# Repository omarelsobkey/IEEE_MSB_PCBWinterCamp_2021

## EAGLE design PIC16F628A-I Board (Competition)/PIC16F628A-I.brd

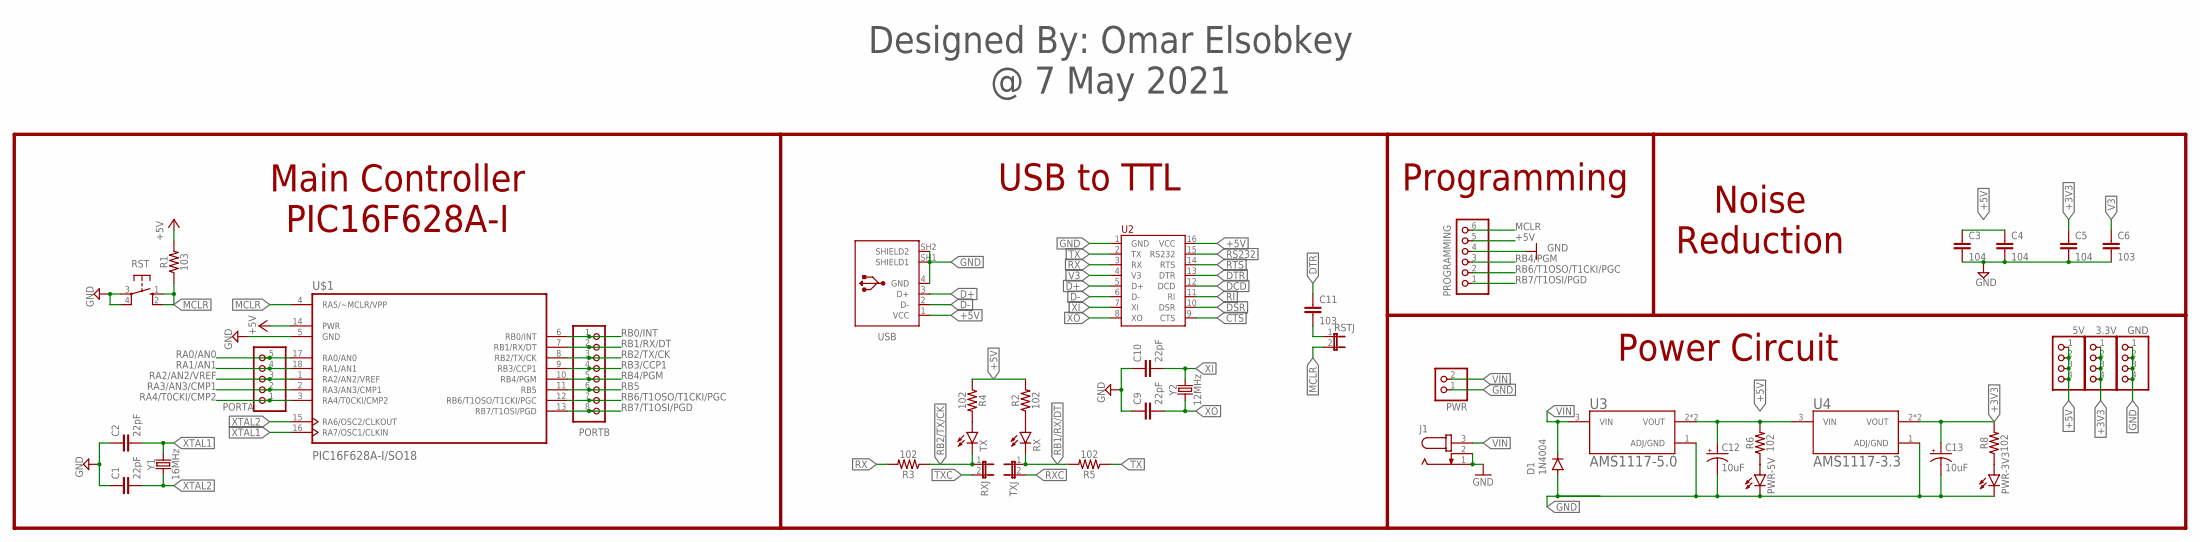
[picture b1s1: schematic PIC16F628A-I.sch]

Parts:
3.3V, 5V: PINHD-1X4; 1X04
C1, C2, C9, C10: 22pF; CAP-PTH-2.54
C3, C4, C5: 104; CAP-PTH-2.54
C6, C11: 103; CAP-PTH-2.54
C12, C13: 10uF; CPOL-RADIAL-2.5MM-5MM-KIT
D1: 1N4004; DO41-10
GND: PINHD-1X4; 1X04
J1: JACK-PLUG0; SPC4077
PORTA: PINHD-1X5; 1X05
PORTB: PINHD-1X8; 1X08
PROGRAMMING: PINHD-1X6; 1X06
PWR: PINHD-1X2; 1X02
PWR-3V3, PWR-5V: LEDCHIP-LED0805; CHIP-LED0805
R1: 103; 1206
R2, R3, R4, R5, R6, R8: 102; 1206
RST: 10-XX; B3F-10XX
RSTJ: JP1E; JP1
RX: LEDCHIP-LED0805; CHIP-LED0805
RXJ: JP1E; JP1
TX: LEDCHIP-LED0805; CHIP-LED0805
TXJ: JP1E; JP1
U2: CH340G; SOP-16
U3: AMS1117-5.0
U4: AMS1117-3.3; AMS1117-5.0
U$1: PIC16F628A-I/SO18; SOIC127P1030X265-18N
USB: 61729-1011; 61729-1011BLF
Y1: 16MHz; HC49U
Y2: 12MHz; HC49U

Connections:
+3V3: 3.3V.1, 3.3V.2, 3.3V.3, 3.3V.4, C5.1, C13.1 (+), R8.2, U4.2 (VOUT), U4.4 (VOUT)
+5V: 5V.1, 5V.2, 5V.3, 5V.4, C3.1, C4.1, C12.1 (+), PROGRAMMING.5, R1.2, R2.2, R4.1, R6.2, U2.16 (VCC), U3.2 (VOUT), U3.4 (VOUT), U4.3 (VIN), U$1.14 (PWR), USB.1 (VCC)
CTS: U2.9 (CTS)
D+: U2.5 (D+), USB.3 (D+)
D-: U2.6 (D-), USB.2 (D-)
DCD: U2.12 (DCD)
DSR: U2.10 (DSR)
DTR: C11.1, U2.13 (DTR)
GND: C1.1, C2.1, C3.2, C4.2, C5.2, C6.2, C9.1, C10.1, C12.2 (-), C13.2 (-), D1.A, GND.1, GND.2, GND.3, GND.4, J1.1, J1.2, PROGRAMMING.4, PWR.1, PWR-3V3.C, PWR-5V.C, RST.3, RST.4 (P1), U2.1 (GND), U3.1 (ADJ/GND), U4.1 (ADJ/GND), U$1.5 (GND), USB.4 (GND), USB.SH1 (SHIELD1), USB.SH2 (SHIELD2)
MCLR: PROGRAMMING.6, R1.1, RST.1 (S), RST.2 (S1), RSTJ.2, U$1.4 (RA5/~MCLR/VPP)
unnamed: R2.1, RX.A
unnamed: R4.2, TX.A
unnamed: PWR-5V.A, R6.1
unnamed: PWR-3V3.A, R8.1
unnamed: C11.2, RSTJ.1
RA0/AN0: PORTA.5, U$1.17 (RA0/AN0)
RA1/AN1: PORTA.4, U$1.18 (RA1/AN1)
RA2/AN2/VREF: PORTA.3, U$1.1 (RA2/AN2/VREF)
RA3/AN3/CMP1: PORTA.2, U$1.2 (RA3/AN3/CMP1)
RA4/T0CKI/CMP2: PORTA.1, U$1.3 (RA4/T0CKI/CMP2)
RB0/INT: PORTB.1, U$1.6 (RB0/INT)
RB1/RX/DT: PORTB.2, R5.2, RX.C, TXJ.1, U$1.7 (RB1/RX/DT)
RB2/TX/CK: PORTB.3, R3.1, RXJ.1, TX.C, U$1.8 (RB2/TX/CK)
RB3/CCP1: PORTB.4, U$1.9 (RB3/CCP1)
RB4/PGM: PORTB.5, PROGRAMMING.3, U$1.10 (RB4/PGM)
RB5: PORTB.6, U$1.11 (RB5)
RB6/T1OSO/T1CKI/PGC: PORTB.7, PROGRAMMING.2, U$1.12 (RB6/T1OSO/T1CKI/PGC)
RB7/T1OSI/PGD: PORTB.8, PROGRAMMING.1, U$1.13 (RB7/T1OSI/PGD)
RI: U2.11 (RI)
RS232: U2.15 (RS232)
RTS: U2.14 (RTS)
RX: R3.2, U2.3 (RX)
RXC: TXJ.2
TX: R5.1, U2.2 (TX)
TXC: RXJ.2
V3: C6.1, U2.4 (V3)
VIN: D1.C, J1.3, PWR.2, U3.3 (VIN)
XI: C10.2, U2.7 (XI), Y2.2
XO: C9.2, U2.8 (XO), Y2.1
XTAL1: C2.2, U$1.16 (RA7/OSC1/CLKIN), Y1.2
XTAL2: C1.2, U$1.15 (RA6/OSC2/CLKOUT), Y1.1

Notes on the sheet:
Main Controller PIC16F628A-I
USB to TTL
Programming
Noise Reduction
Power Circuit
Designed By: Omar Elsobkey @ 7 May 2021

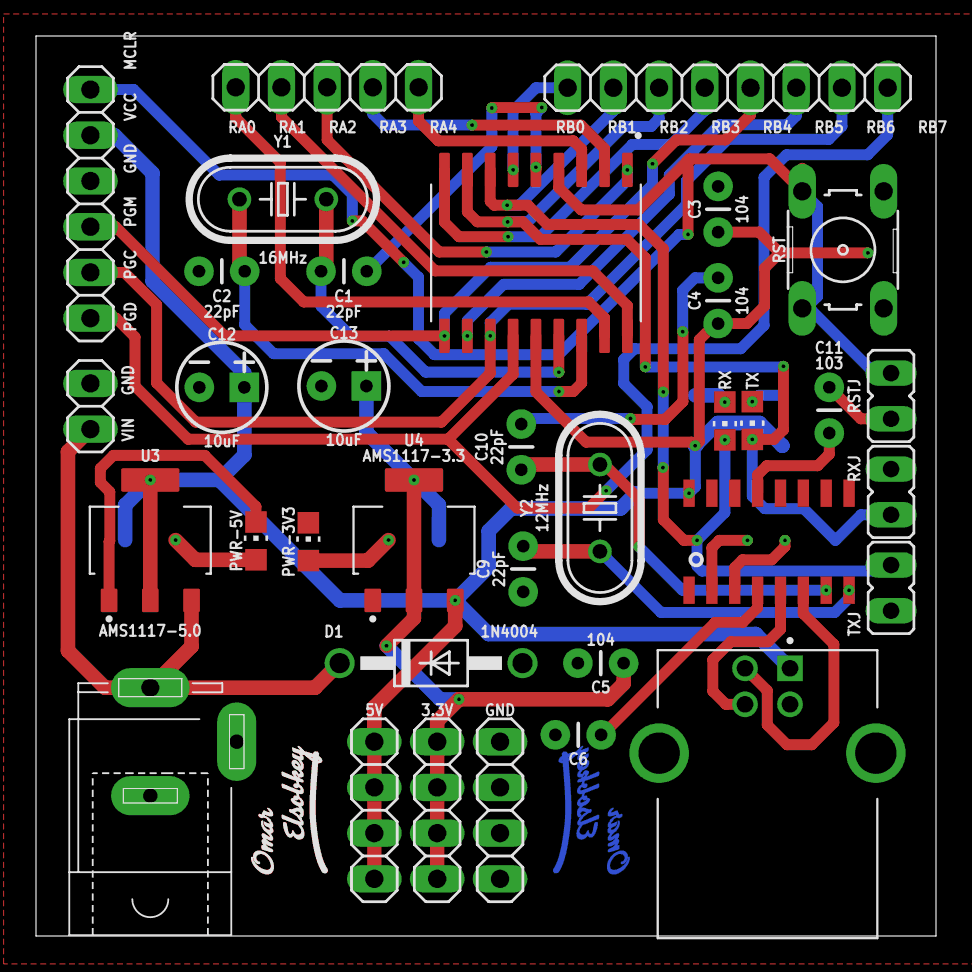
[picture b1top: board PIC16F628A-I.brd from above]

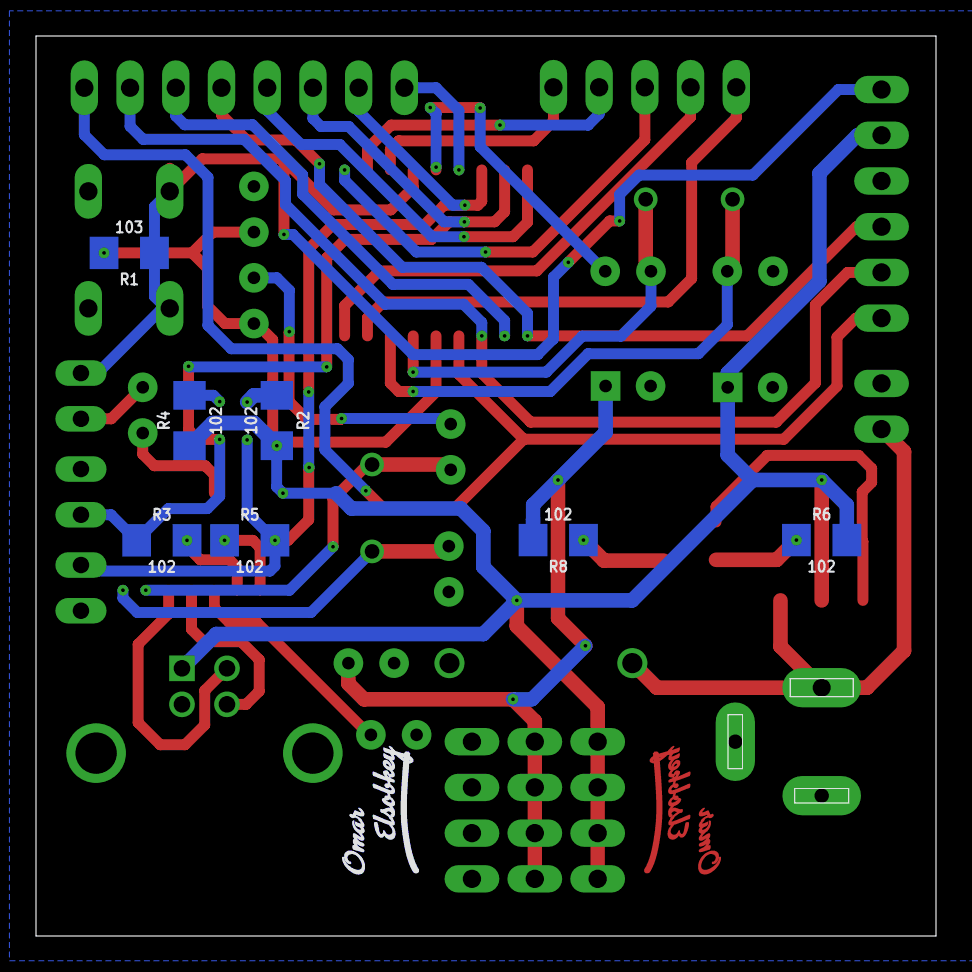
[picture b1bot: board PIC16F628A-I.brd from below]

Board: 2 copper layers, 50.0 x 50.0 mm, 46 parts (9 on the bottom side), 33 nets.

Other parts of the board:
U$2, U$3: OMAR_ELSOBKEY_X0.5_TN
U$4, U$5: OMAR_ELSOBKEY_X0.5_T

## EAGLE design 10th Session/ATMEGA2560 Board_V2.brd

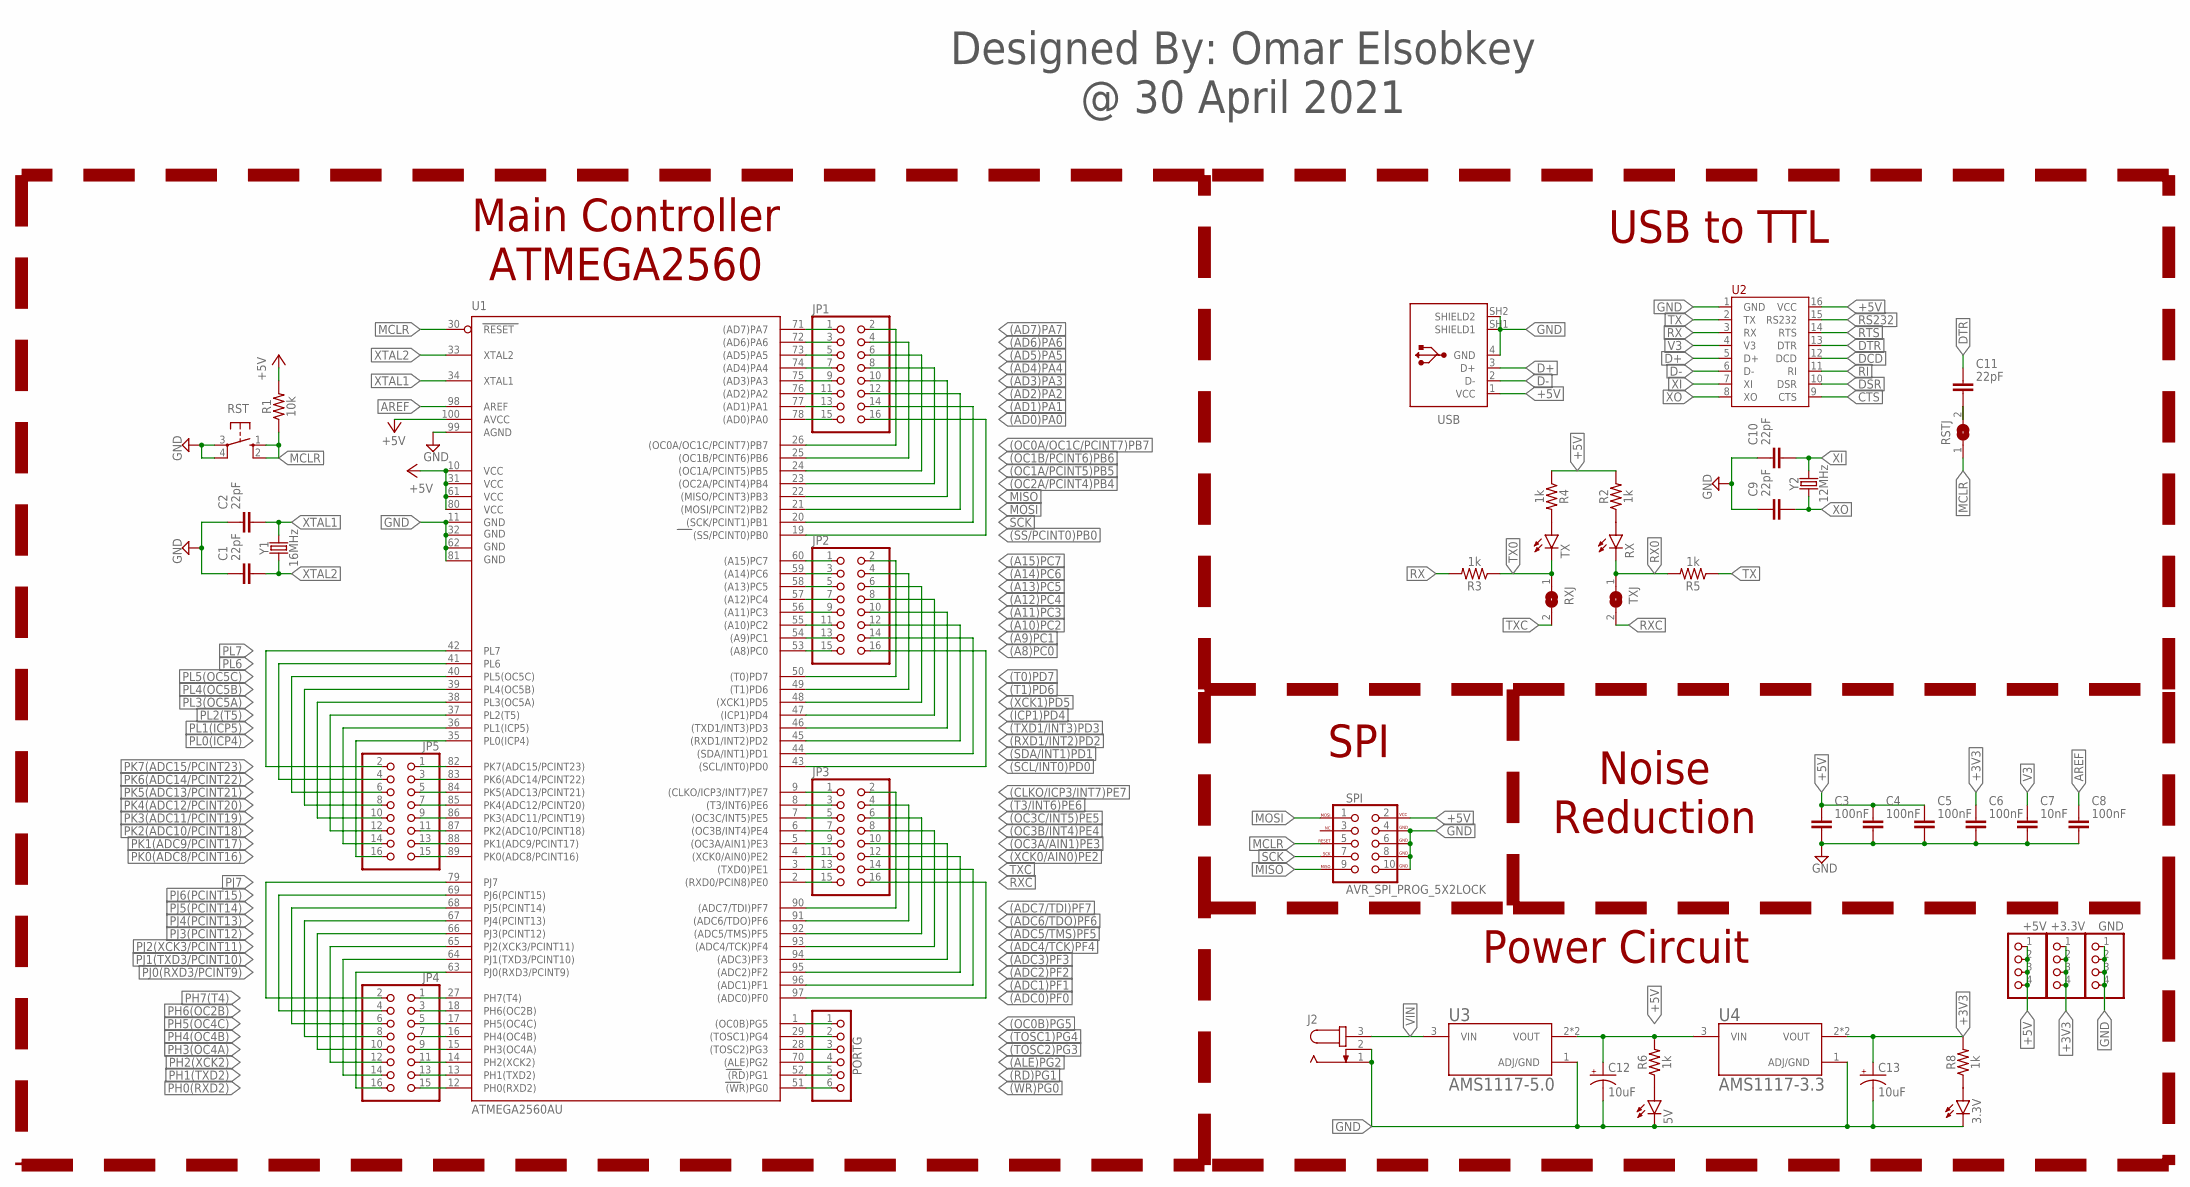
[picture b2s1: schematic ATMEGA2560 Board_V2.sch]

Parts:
3.3V, 5V: LEDCHIP-LED0805; CHIP-LED0805
+3.3V, +5V: PINHD-1X4; 1X04
C1, C2, C9, C10, C11: 22pF; CAPC2012X110
C3, C4, C5, C6, C8: 100nF; CAPC2012X110
C7: 10nF; CAPC2012X110
C12, C13: 10uF; CPOL-RADIAL-2.5MM-5MM-KIT
GND: PINHD-1X4; 1X04
J2: JACK-PLUG0; SPC4077
JP1, JP2, JP3, JP4, JP5: PINHD-2X8; 2X08
PORTG: PINHD-1X6; 1X06
R1: 10k; 1206
R2, R3, R4, R5, R6, R8: 1k; 1206
RST: 10-XX; B3F-10XX
RSTJ: SJW
RX: LEDCHIP-LED0805; CHIP-LED0805
RXJ: SJW
SPI: AVR_SPI_PROG_5X2LOCK; 2X5-SHROUDED_LOCK
TX: LEDCHIP-LED0805; CHIP-LED0805
TXJ: SJW
U1: ATMEGA2560AU; TQFP100
U2: CH340G; SOP-16
U3: AMS1117-5.0
U4: AMS1117-3.3; AMS1117-5.0
USB: 61729-1011; 61729-1011BLF
Y1: 16MHz; HC49U
Y2: 12MHz; HC49U

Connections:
(A8)PC0: JP2.15, U1.53 ((A8)PC0)
(A9)PC1: JP2.13, U1.54 ((A9)PC1)
(A10)PC2: JP2.11, U1.55 ((A10)PC2)
(A11)PC3: JP2.9, U1.56 ((A11)PC3)
(A12)PC4: JP2.7, U1.57 ((A12)PC4)
(A13)PC5: JP2.5, U1.58 ((A13)PC5)
(A14)PC6: JP2.3, U1.59 ((A14)PC6)
(A15)PC7: JP2.1, U1.60 ((A15)PC7)
(AD0)PA0: JP1.15, U1.78 ((AD0)PA0)
(AD1)PA1: JP1.13, U1.77 ((AD1)PA1)
(AD2)PA2: JP1.11, U1.76 ((AD2)PA2)
(AD3)PA3: JP1.9, U1.75 ((AD3)PA3)
(AD4)PA4: JP1.7, U1.74 ((AD4)PA4)
(AD5)PA5: JP1.5, U1.73 ((AD5)PA5)
(AD6)PA6: JP1.3, U1.72 ((AD6)PA6)
(AD7)PA7: JP1.1, U1.71 ((AD7)PA7)
(ADC0)PF0: JP3.16, U1.97 ((ADC0)PF0)
(ADC1)PF1: JP3.14, U1.96 ((ADC1)PF1)
(ADC2)PF2: JP3.12, U1.95 ((ADC2)PF2)
(ADC3)PF3: JP3.10, U1.94 ((ADC3)PF3)
(ADC4/TCK)PF4: JP3.8, U1.93 ((ADC4/TCK)PF4)
(ADC5/TMS)PF5: JP3.6, U1.92 ((ADC5/TMS)PF5)
(ADC6/TDO)PF6: JP3.4, U1.91 ((ADC6/TDO)PF6)
(ADC7/TDI)PF7: JP3.2, U1.90 ((ADC7/TDI)PF7)
(ALE)PG2: PORTG.4, U1.70 ((ALE)PG2)
(CLKO/ICP3/INT7)PE7: JP3.1, U1.9 ((CLKO/ICP3/INT7)PE7)
(ICP1)PD4: JP2.8, U1.47 ((ICP1)PD4)
(OC0A/OC1C/PCINT7)PB7: JP1.2, U1.26 ((OC0A/OC1C/PCINT7)PB7)
(OC0B)PG5: PORTG.1, U1.1 ((OC0B)PG5)
(OC1A/PCINT5)PB5: JP1.6, U1.24 ((OC1A/PCINT5)PB5)
(OC1B/PCINT6)PB6: JP1.4, U1.25 ((OC1B/PCINT6)PB6)
(OC2A/PCINT4)PB4: JP1.8, U1.23 ((OC2A/PCINT4)PB4)
(OC3A/AIN1)PE3: JP3.9, U1.5 ((OC3A/AIN1)PE3)
(OC3B/INT4)PE4: JP3.7, U1.6 ((OC3B/INT4)PE4)
(OC3C/INT5)PE5: JP3.5, U1.7 ((OC3C/INT5)PE5)
(RD)PG1: PORTG.5, U1.52 ((RD)PG1)
(RXD1/INT2)PD2: JP2.12, U1.45 ((RXD1/INT2)PD2)
(SCL/INT0)PD0: JP2.16, U1.43 ((SCL/INT0)PD0)
(SDA/INT1)PD1: JP2.14, U1.44 ((SDA/INT1)PD1)
(SS/PCINT0)PB0: JP1.16, U1.19 ((SS/PCINT0)PB0)
(T0)PD7: JP2.2, U1.50 ((T0)PD7)
(T1)PD6: JP2.4, U1.49 ((T1)PD6)
(T3/INT6)PE6: JP3.3, U1.8 ((T3/INT6)PE6)
(TOSC1)PG4: PORTG.2, U1.29 ((TOSC1)PG4)
(TOSC2)PG3: PORTG.3, U1.28 ((TOSC2)PG3)
(TXD1/INT3)PD3: JP2.10, U1.46 ((TXD1/INT3)PD3)
(WR)PG0: PORTG.6, U1.51 ((WR)PG0)
(XCK0/AIN0)PE2: JP3.11, U1.4 ((XCK0/AIN0)PE2)
(XCK1)PD5: JP2.6, U1.48 ((XCK1)PD5)
+3V3: +3.3V.1, +3.3V.2, +3.3V.3, +3.3V.4, C6.1, C13.1 (+), R8.2, U4.2 (VOUT), U4.4 (VOUT)
+5V: +5V.1, +5V.2, +5V.3, +5V.4, C3.1, C4.1, C5.1, C12.1 (+), R1.2, R2.2, R4.1, R6.2, SPI.2 (VCC), U1.10 (VCC), U1.31 (VCC1), U1.61 (VCC2), U1.80 (VCC3), U1.100 (AVCC), U2.16 (VCC), U3.2 (VOUT), U3.4 (VOUT), U4.3 (VIN), USB.1 (VCC)
AREF: C8.1, U1.98 (AREF)
CTS: U2.9 (CTS)
D+: U2.5 (D+), USB.3 (D+)
D-: U2.6 (D-), USB.2 (D-)
DCD: U2.12 (DCD)
DSR: U2.10 (DSR)
DTR: C11.1, U2.13 (DTR)
GND: 3.3V.C, 5V.C, C1.1, C2.1, C3.2, C4.2, C5.2, C6.2, C7.2, C8.2, C9.1, C10.1, C12.2 (-), C13.2 (-), GND.1, GND.2, GND.3, GND.4, J2.1, J2.2, RST.3, RST.4 (P1), SPI.4 (GND), SPI.6 (GND), SPI.8 (GND), SPI.10 (GND), U1.11 (GND), U1.32 (GND1), U1.62 (GND2), U1.81 (GND3), U1.99 (AGND), U2.1 (GND), U3.1 (ADJ/GND), U4.1 (ADJ/GND), USB.4 (GND), USB.SH1 (SHIELD1), USB.SH2 (SHIELD2)
MCLR: R1.1, RST.1 (S), RST.2 (S1), RSTJ.1, SPI.5 (RESET), U1.30 (RESET)
MISO: JP1.10, SPI.9 (MISO), U1.22 ((MISO/PCINT3)PB3)
MOSI: JP1.12, SPI.1 (MOSI), U1.21 ((MOSI/PCINT2)PB2)
unnamed: R2.1, RX.A
unnamed: R4.2, TX.A
unnamed: 5V.A, R6.1
unnamed: 3.3V.A, R8.1
unnamed: C11.2, RSTJ.2
PH0(RXD2): JP4.15, U1.12 (PH0(RXD2))
PH1(TXD2): JP4.13, U1.13 (PH1(TXD2))
PH2(XCK2): JP4.11, U1.14 (PH2(XCK2))
PH3(OC4A): JP4.9, U1.15 (PH3(OC4A))
PH4(OC4B): JP4.7, U1.16 (PH4(OC4B))
PH5(OC4C): JP4.5, U1.17 (PH5(OC4C))
PH6(OC2B): JP4.3, U1.18 (PH6(OC2B))
PH7(T4): JP4.1, U1.27 (PH7(T4))
PJ0(RXD3/PCINT9): JP4.16, U1.63 (PJ0(RXD3/PCINT9))
PJ1(TXD3/PCINT10): JP4.14, U1.64 (PJ1(TXD3/PCINT10))
PJ2(XCK3/PCINT11): JP4.12, U1.65 (PJ2(XCK3/PCINT11))
PJ3(PCINT12): JP4.10, U1.66 (PJ3(PCINT12))
PJ4(PCINT13): JP4.8, U1.67 (PJ4(PCINT13))
PJ5(PCINT14): JP4.6, U1.68 (PJ5(PCINT14))
PJ6(PCINT15): JP4.4, U1.69 (PJ6(PCINT15))
PJ7: JP4.2, U1.79 (PJ7)
PK0(ADC8/PCINT16): JP5.15, U1.89 (PK0(ADC8/PCINT16))
PK1(ADC9/PCINT17): JP5.13, U1.88 (PK1(ADC9/PCINT17))
PK2(ADC10/PCINT18): JP5.11, U1.87 (PK2(ADC10/PCINT18))
PK3(ADC11/PCINT19): JP5.9, U1.86 (PK3(ADC11/PCINT19))
PK4(ADC12/PCINT20): JP5.7, U1.85 (PK4(ADC12/PCINT20))
PK5(ADC13/PCINT21): JP5.5, U1.84 (PK5(ADC13/PCINT21))
PK6(ADC14/PCINT22): JP5.3, U1.83 (PK6(ADC14/PCINT22))
PK7(ADC15/PCINT23): JP5.1, U1.82 (PK7(ADC15/PCINT23))
PL0(ICP4): JP5.16, U1.35 (PL0(ICP4))
PL1(ICP5): JP5.14, U1.36 (PL1(ICP5))
PL2(T5): JP5.12, U1.37 (PL2(T5))
PL3(OC5A): JP5.10, U1.38 (PL3(OC5A))
PL4(OC5B): JP5.8, U1.39 (PL4(OC5B))
PL5(OC5C): JP5.6, U1.40 (PL5(OC5C))
PL6: JP5.4, U1.41 (PL6)
PL7: JP5.2, U1.42 (PL7)
RI: U2.11 (RI)
RS232: U2.15 (RS232)
RTS: U2.14 (RTS)
RX: R3.2, U2.3 (RX)
RX0: R5.2, RX.C, TXJ.1
RXC: JP3.15, TXJ.2, U1.2 ((RXD0/PCIN8)PE0)
SCK: JP1.14, SPI.7 (SCK), U1.20 ((SCK/PCINT1)PB1)
TX: R5.1, U2.2 (TX)
TX0: R3.1, RXJ.1, TX.C
TXC: JP3.13, RXJ.2, U1.3 ((TXD0)PE1)
V3: C7.1, U2.4 (V3)
VIN: J2.3, U3.3 (VIN)
XI: C10.2, U2.7 (XI), Y2.2
XO: C9.2, U2.8 (XO), Y2.1
XTAL1: C2.2, U1.34 (XTAL1), Y1.2
XTAL2: C1.2, U1.33 (XTAL2), Y1.1

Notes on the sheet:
Main Controller ATMEGA2560
USB to TTL
SPI
Noise Reduction
Power Circuit
Designed By: Omar Elsobkey @ 30 April 2021

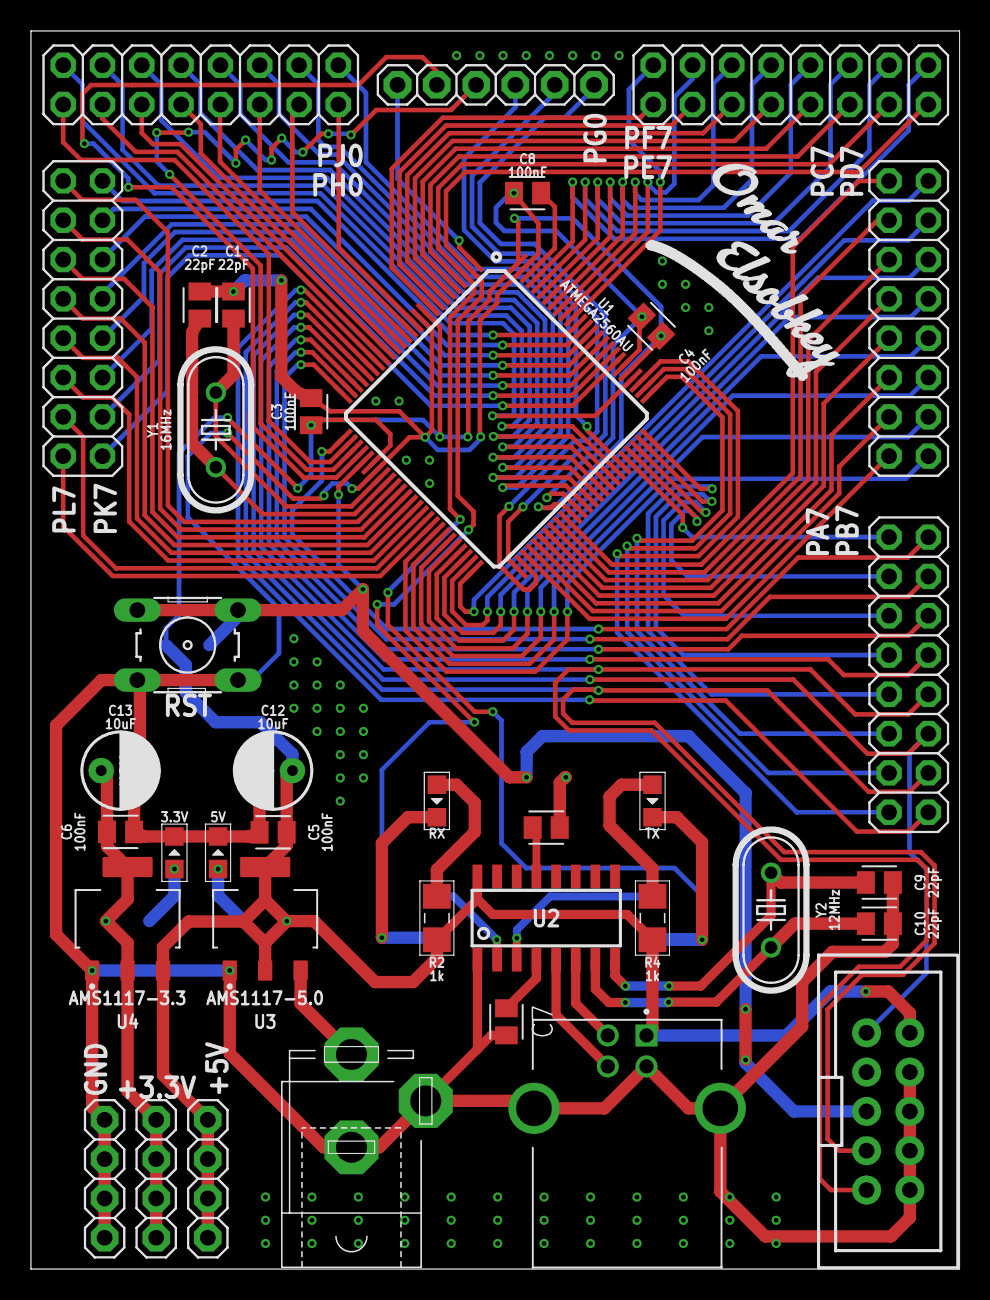
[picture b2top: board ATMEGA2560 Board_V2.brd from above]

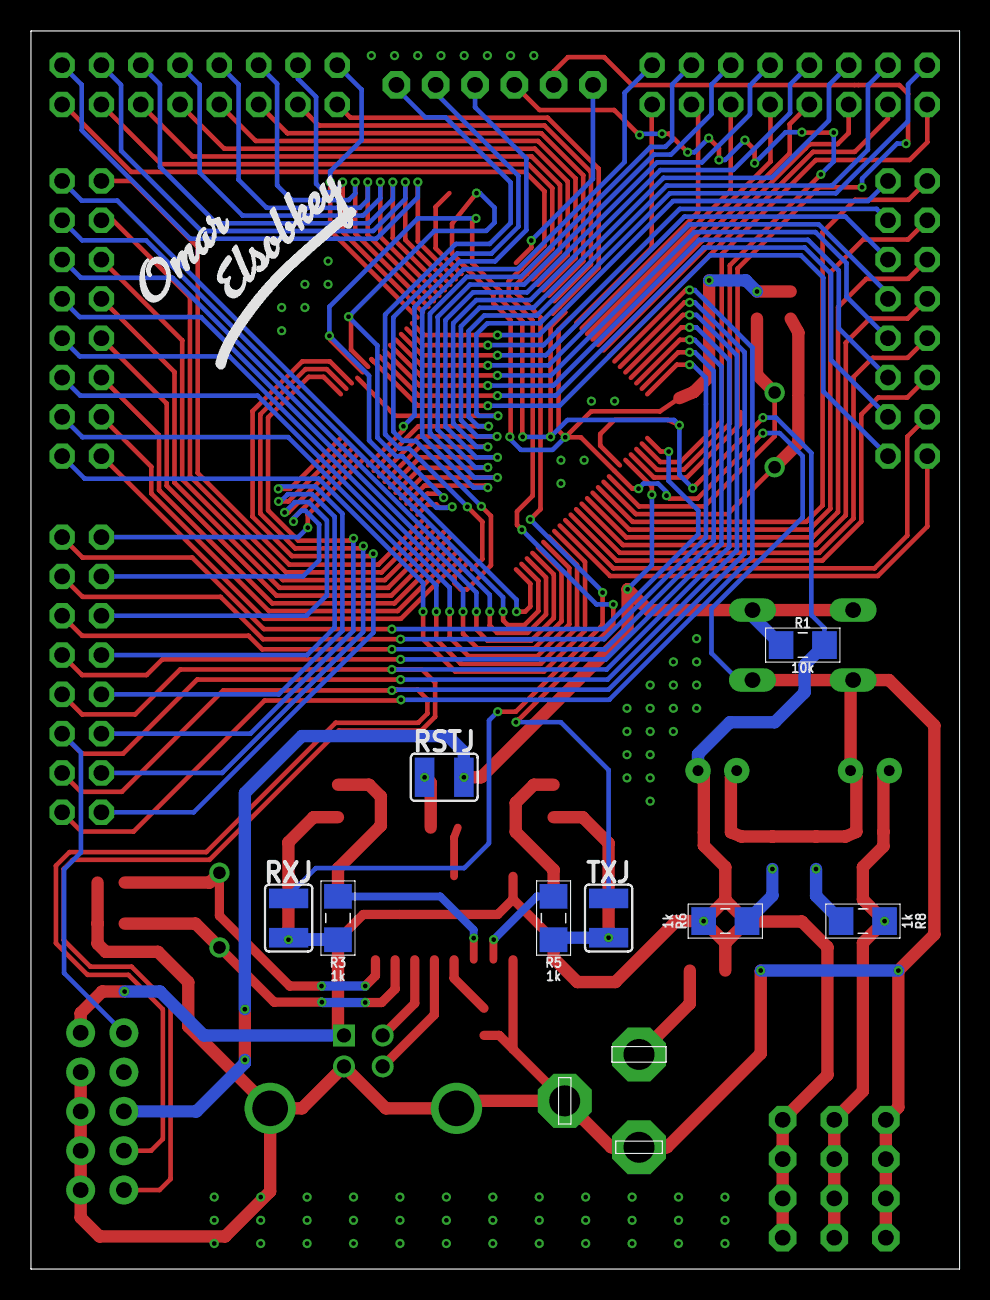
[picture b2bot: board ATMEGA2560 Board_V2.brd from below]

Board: 2 copper layers, 60.0 x 80.0 mm, 48 parts (9 on the bottom side), 109 nets.

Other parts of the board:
U$1, U$2: OMAR_ELSOBKEY_X1

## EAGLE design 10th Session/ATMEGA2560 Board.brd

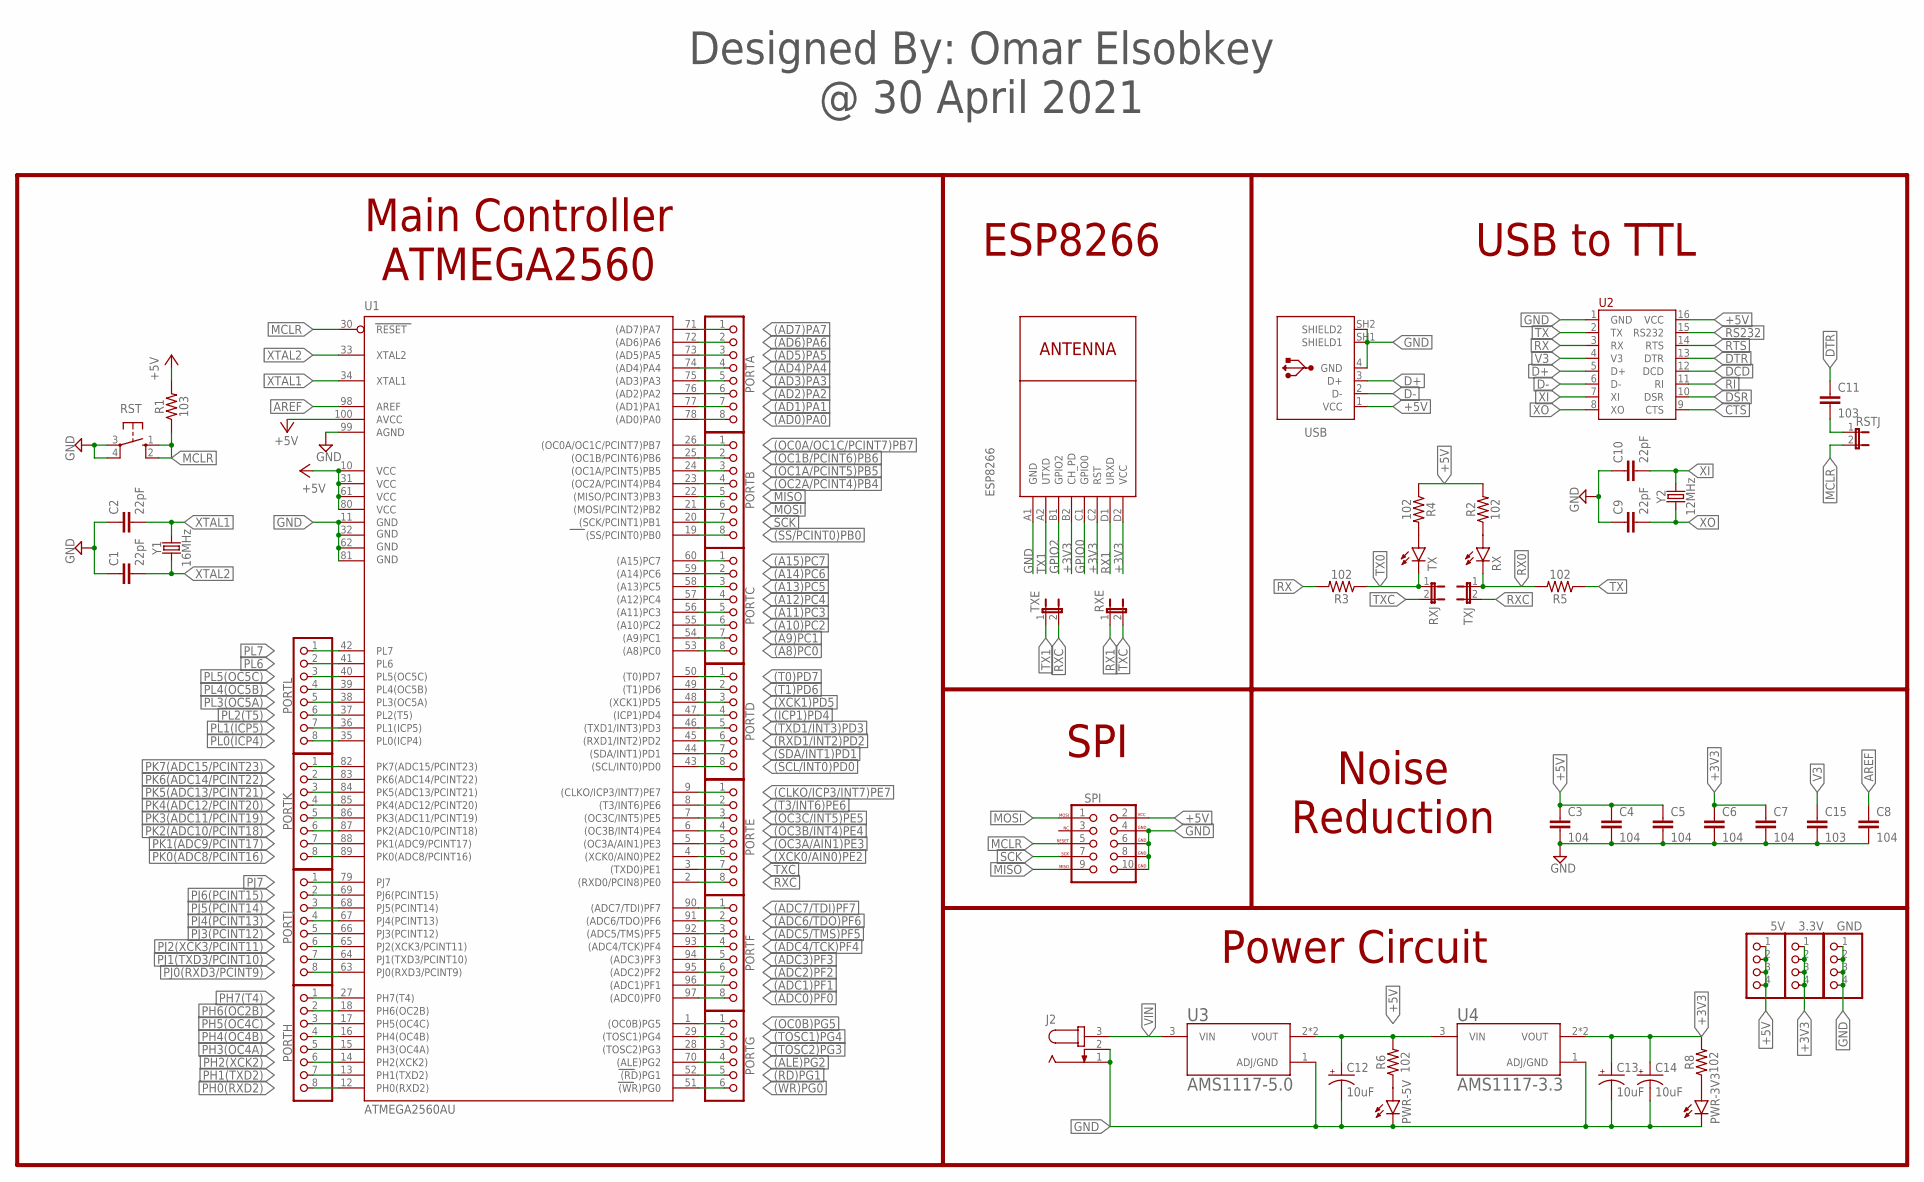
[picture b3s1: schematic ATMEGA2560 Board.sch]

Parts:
3.3V, 5V: PINHD-1X4; 1X04
C1, C2, C9, C10: 22pF; CAP-PTH-2.54
C3, C4, C5, C6, C7, C8: 104; CAP-PTH-2.54
C11, C15: 103; CAP-PTH-2.54
C12, C13, C14: 10uF; CPOL-RADIAL-2.5MM-5MM-KIT
ESP8266: WIRELESS-WIFI-ESP-01
GND: PINHD-1X4; 1X04
J2: JACK-PLUG0; SPC4077
PORTA: PINHD-1X8; 1X08
PORTB: PINHD-1X8; 1X08
PORTC: PINHD-1X8; 1X08
PORTD: PINHD-1X8; 1X08
PORTE: PINHD-1X8; 1X08
PORTF: PINHD-1X8; 1X08
PORTG: PINHD-1X6; 1X06
PORTH: PINHD-1X8; 1X08
PORTJ: PINHD-1X8; 1X08
PORTK: PINHD-1X8; 1X08
PORTL: PINHD-1X8; 1X08
PWR-3V3, PWR-5V: LEDCHIP-LED0805; CHIP-LED0805
R1: 103; 1206
R2, R3, R4, R5, R6, R8: 102; 1206
RST: 10-XX; B3F-10XX
RSTJ: JP1E; JP1
RX: LEDCHIP-LED0805; CHIP-LED0805
RXE: JP1E; JP1
RXJ: JP1E; JP1
SPI: AVR_SPI_PROG_5X2LOCK; 2X5-SHROUDED_LOCK
TX: LEDCHIP-LED0805; CHIP-LED0805
TXE: JP1E; JP1
TXJ: JP1E; JP1
U1: ATMEGA2560AU; TQFP100
U2: CH340G; SOP-16
U3: AMS1117-5.0
U4: AMS1117-3.3; AMS1117-5.0
USB: 61729-1011; 61729-1011BLF
Y1: 16MHz; HC49U
Y2: 12MHz; HC49U

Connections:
(A8)PC0: PORTC.8, U1.53 ((A8)PC0)
(A9)PC1: PORTC.7, U1.54 ((A9)PC1)
(A10)PC2: PORTC.6, U1.55 ((A10)PC2)
(A11)PC3: PORTC.5, U1.56 ((A11)PC3)
(A12)PC4: PORTC.4, U1.57 ((A12)PC4)
(A13)PC5: PORTC.3, U1.58 ((A13)PC5)
(A14)PC6: PORTC.2, U1.59 ((A14)PC6)
(A15)PC7: PORTC.1, U1.60 ((A15)PC7)
(AD0)PA0: PORTA.8, U1.78 ((AD0)PA0)
(AD1)PA1: PORTA.7, U1.77 ((AD1)PA1)
(AD2)PA2: PORTA.6, U1.76 ((AD2)PA2)
(AD3)PA3: PORTA.5, U1.75 ((AD3)PA3)
(AD4)PA4: PORTA.4, U1.74 ((AD4)PA4)
(AD5)PA5: PORTA.3, U1.73 ((AD5)PA5)
(AD6)PA6: PORTA.2, U1.72 ((AD6)PA6)
(AD7)PA7: PORTA.1, U1.71 ((AD7)PA7)
(ADC0)PF0: PORTF.8, U1.97 ((ADC0)PF0)
(ADC1)PF1: PORTF.7, U1.96 ((ADC1)PF1)
(ADC2)PF2: PORTF.6, U1.95 ((ADC2)PF2)
(ADC3)PF3: PORTF.5, U1.94 ((ADC3)PF3)
(ADC4/TCK)PF4: PORTF.4, U1.93 ((ADC4/TCK)PF4)
(ADC5/TMS)PF5: PORTF.3, U1.92 ((ADC5/TMS)PF5)
(ADC6/TDO)PF6: PORTF.2, U1.91 ((ADC6/TDO)PF6)
(ADC7/TDI)PF7: PORTF.1, U1.90 ((ADC7/TDI)PF7)
(ALE)PG2: PORTG.4, U1.70 ((ALE)PG2)
(CLKO/ICP3/INT7)PE7: PORTE.1, U1.9 ((CLKO/ICP3/INT7)PE7)
(ICP1)PD4: PORTD.4, U1.47 ((ICP1)PD4)
(OC0A/OC1C/PCINT7)PB7: PORTB.1, U1.26 ((OC0A/OC1C/PCINT7)PB7)
(OC0B)PG5: PORTG.1, U1.1 ((OC0B)PG5)
(OC1A/PCINT5)PB5: PORTB.3, U1.24 ((OC1A/PCINT5)PB5)
(OC1B/PCINT6)PB6: PORTB.2, U1.25 ((OC1B/PCINT6)PB6)
(OC2A/PCINT4)PB4: PORTB.4, U1.23 ((OC2A/PCINT4)PB4)
(OC3A/AIN1)PE3: PORTE.5, U1.5 ((OC3A/AIN1)PE3)
(OC3B/INT4)PE4: PORTE.4, U1.6 ((OC3B/INT4)PE4)
(OC3C/INT5)PE5: PORTE.3, U1.7 ((OC3C/INT5)PE5)
(RD)PG1: PORTG.5, U1.52 ((RD)PG1)
(RXD1/INT2)PD2: PORTD.6, U1.45 ((RXD1/INT2)PD2)
(SCL/INT0)PD0: PORTD.8, U1.43 ((SCL/INT0)PD0)
(SDA/INT1)PD1: PORTD.7, U1.44 ((SDA/INT1)PD1)
(SS/PCINT0)PB0: PORTB.8, U1.19 ((SS/PCINT0)PB0)
(T0)PD7: PORTD.1, U1.50 ((T0)PD7)
(T1)PD6: PORTD.2, U1.49 ((T1)PD6)
(T3/INT6)PE6: PORTE.2, U1.8 ((T3/INT6)PE6)
(TOSC1)PG4: PORTG.2, U1.29 ((TOSC1)PG4)
(TOSC2)PG3: PORTG.3, U1.28 ((TOSC2)PG3)
(TXD1/INT3)PD3: PORTD.5, U1.46 ((TXD1/INT3)PD3)
(WR)PG0: PORTG.6, U1.51 ((WR)PG0)
(XCK0/AIN0)PE2: PORTE.6, U1.4 ((XCK0/AIN0)PE2)
(XCK1)PD5: PORTD.3, U1.48 ((XCK1)PD5)
+3V3: 3.3V.1, 3.3V.2, 3.3V.3, 3.3V.4, C6.1, C7.1, C13.1 (+), C14.1 (+), ESP8266.B2 (CH_PD), ESP8266.C2 (RST), ESP8266.D2 (VCC), R8.2, U4.2 (VOUT), U4.4 (VOUT)
+5V: 5V.1, 5V.2, 5V.3, 5V.4, C3.1, C4.1, C5.1, C12.1 (+), R1.2, R2.2, R4.1, R6.2, SPI.2 (VCC), U1.10 (VCC), U1.31 (VCC1), U1.61 (VCC2), U1.80 (VCC3), U1.100 (AVCC), U2.16 (VCC), U3.2 (VOUT), U3.4 (VOUT), U4.3 (VIN), USB.1 (VCC)
AREF: C8.1, U1.98 (AREF)
CTS: U2.9 (CTS)
D+: U2.5 (D+), USB.3 (D+)
D-: U2.6 (D-), USB.2 (D-)
DCD: U2.12 (DCD)
DSR: U2.10 (DSR)
DTR: C11.1, U2.13 (DTR)
GND: C1.1, C2.1, C3.2, C4.2, C5.2, C6.2, C7.2, C8.2, C9.1, C10.1, C12.2 (-), C13.2 (-), C14.2 (-), C15.2, ESP8266.A1 (GND), GND.1, GND.2, GND.3, GND.4, J2.1, J2.2, PWR-3V3.C, PWR-5V.C, RST.3, RST.4 (P1), SPI.4 (GND), SPI.6 (GND), SPI.8 (GND), SPI.10 (GND), U1.11 (GND), U1.32 (GND1), U1.62 (GND2), U1.81 (GND3), U1.99 (AGND), U2.1 (GND), U3.1 (ADJ/GND), U4.1 (ADJ/GND), USB.4 (GND), USB.SH1 (SHIELD1), USB.SH2 (SHIELD2)
GPIO0: ESP8266.C1 (GPIO0)
GPIO2: ESP8266.B1 (GPIO2)
MCLR: R1.1, RST.1 (S), RST.2 (S1), RSTJ.2, SPI.5 (RESET), U1.30 (RESET)
MISO: PORTB.5, SPI.9 (MISO), U1.22 ((MISO/PCINT3)PB3)
MOSI: PORTB.6, SPI.1 (MOSI), U1.21 ((MOSI/PCINT2)PB2)
unnamed: R2.1, RX.A
unnamed: R4.2, TX.A
unnamed: PWR-5V.A, R6.1
unnamed: PWR-3V3.A, R8.1
unnamed: C11.2, RSTJ.1
PH0(RXD2): PORTH.8, U1.12 (PH0(RXD2))
PH1(TXD2): PORTH.7, U1.13 (PH1(TXD2))
PH2(XCK2): PORTH.6, U1.14 (PH2(XCK2))
PH3(OC4A): PORTH.5, U1.15 (PH3(OC4A))
PH4(OC4B): PORTH.4, U1.16 (PH4(OC4B))
PH5(OC4C): PORTH.3, U1.17 (PH5(OC4C))
PH6(OC2B): PORTH.2, U1.18 (PH6(OC2B))
PH7(T4): PORTH.1, U1.27 (PH7(T4))
PJ0(RXD3/PCINT9): PORTJ.8, U1.63 (PJ0(RXD3/PCINT9))
PJ1(TXD3/PCINT10): PORTJ.7, U1.64 (PJ1(TXD3/PCINT10))
PJ2(XCK3/PCINT11): PORTJ.6, U1.65 (PJ2(XCK3/PCINT11))
PJ3(PCINT12): PORTJ.5, U1.66 (PJ3(PCINT12))
PJ4(PCINT13): PORTJ.4, U1.67 (PJ4(PCINT13))
PJ5(PCINT14): PORTJ.3, U1.68 (PJ5(PCINT14))
PJ6(PCINT15): PORTJ.2, U1.69 (PJ6(PCINT15))
PJ7: PORTJ.1, U1.79 (PJ7)
PK0(ADC8/PCINT16): PORTK.8, U1.89 (PK0(ADC8/PCINT16))
PK1(ADC9/PCINT17): PORTK.7, U1.88 (PK1(ADC9/PCINT17))
PK2(ADC10/PCINT18): PORTK.6, U1.87 (PK2(ADC10/PCINT18))
PK3(ADC11/PCINT19): PORTK.5, U1.86 (PK3(ADC11/PCINT19))
PK4(ADC12/PCINT20): PORTK.4, U1.85 (PK4(ADC12/PCINT20))
PK5(ADC13/PCINT21): PORTK.3, U1.84 (PK5(ADC13/PCINT21))
PK6(ADC14/PCINT22): PORTK.2, U1.83 (PK6(ADC14/PCINT22))
PK7(ADC15/PCINT23): PORTK.1, U1.82 (PK7(ADC15/PCINT23))
PL0(ICP4): PORTL.8, U1.35 (PL0(ICP4))
PL1(ICP5): PORTL.7, U1.36 (PL1(ICP5))
PL2(T5): PORTL.6, U1.37 (PL2(T5))
PL3(OC5A): PORTL.5, U1.38 (PL3(OC5A))
PL4(OC5B): PORTL.4, U1.39 (PL4(OC5B))
PL5(OC5C): PORTL.3, U1.40 (PL5(OC5C))
PL6: PORTL.2, U1.41 (PL6)
PL7: PORTL.1, U1.42 (PL7)
RI: U2.11 (RI)
RS232: U2.15 (RS232)
RTS: U2.14 (RTS)
RX: R3.2, U2.3 (RX)
RX0: R5.2, RX.C, TXJ.1
RX1: ESP8266.D1 (URXD), RXE.1
RXC: PORTE.8, TXE.2, TXJ.2, U1.2 ((RXD0/PCIN8)PE0)
SCK: PORTB.7, SPI.7 (SCK), U1.20 ((SCK/PCINT1)PB1)
TX: R5.1, U2.2 (TX)
TX0: R3.1, RXJ.1, TX.C
TX1: ESP8266.A2 (UTXD), TXE.1
TXC: PORTE.7, RXE.2, RXJ.2, U1.3 ((TXD0)PE1)
V3: C15.1, U2.4 (V3)
VIN: J2.3, U3.3 (VIN)
XI: C10.2, U2.7 (XI), Y2.2
XO: C9.2, U2.8 (XO), Y2.1
XTAL1: C2.2, U1.34 (XTAL1), Y1.2
XTAL2: C1.2, U1.33 (XTAL2), Y1.1

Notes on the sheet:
Main Controller ATMEGA2560
ESP8266
USB to TTL
SPI
Noise Reduction
Power Circuit
Designed By: Omar Elsobkey @ 30 April 2021

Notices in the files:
parts and their libraries:
SparkFun-Capacitors: Licensing: Creative Commons ShareAlike 4.0 International - https://creativecommons.org/licenses/by-sa/4.0
Modules: Released under the Creative Commons Attribution 4.0 International License: http://creativecommons.org/licenses/by/4.0
